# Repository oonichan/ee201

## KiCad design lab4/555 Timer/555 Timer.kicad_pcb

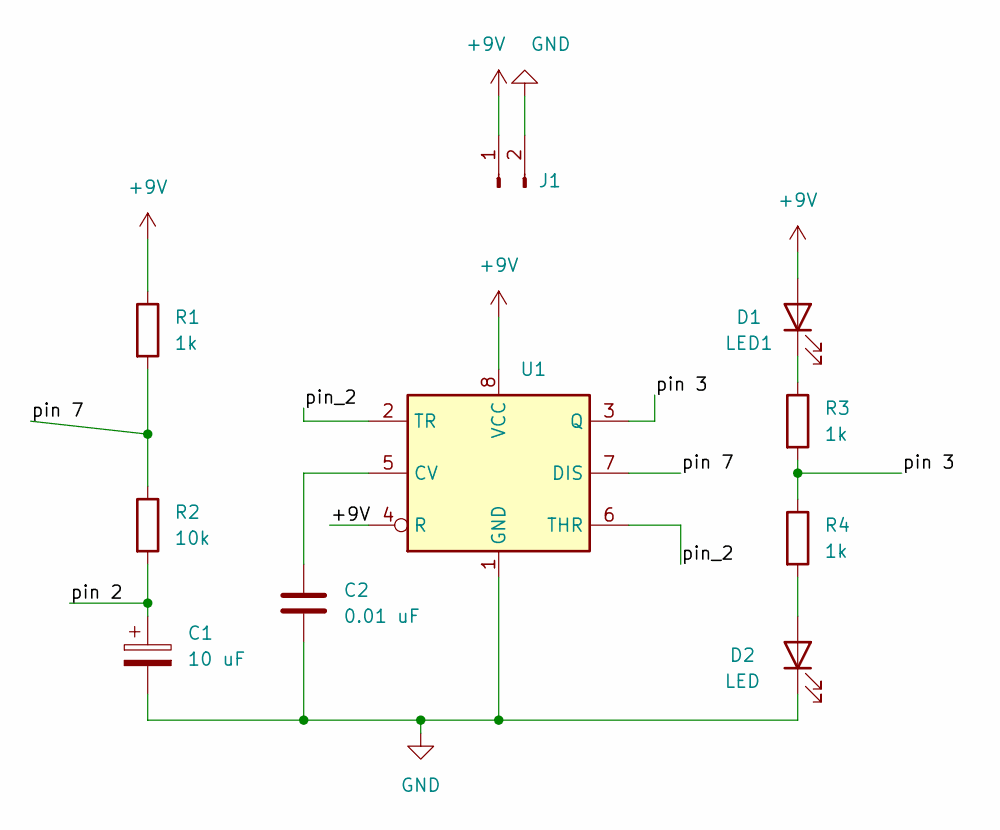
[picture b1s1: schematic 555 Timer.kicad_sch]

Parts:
C1: 10 uF; CP_EIA-3216-18_Kemet-A_Pad1.58x1.35mm_HandSolder
C2: 0.01 uF; C_0805_2012Metric_Pad1.18x1.45mm_HandSolder
D2: LED; LED_1206_3216Metric_Pad1.42x1.75mm_HandSolder
J1: Conn_01x02_Male; TerminalBlock_bornier-2_P5.08mm
LED1: D1; LED_1206_3216Metric_Pad1.42x1.75mm_HandSolder
R1, R3, R4: 1k; R_0805_2012Metric_Pad1.20x1.40mm_HandSolder
R2: 10k; R_0805_2012Metric_Pad1.20x1.40mm_HandSolder
U1: NE555D; SOIC-8-1EP_3.9x4.9mm_P1.27mm_EP2.29x3mm

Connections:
+9V: J1.1, LED1.2 (A), R1.1, U1.4 (R), U1.8 (VCC)
/pin 2: C1.1, R2.2
/pin 3: R3.2, R4.1, U1.3 (Q)
/pin 7: R1.2, R2.1, U1.7 (DIS)
/pin_2: U1.2 (TR), U1.6 (THR)
GND: C1.2, C2.2, D2.1 (K), J1.2, U1.1 (GND)
unnamed: C2.1, U1.5 (CV)
unnamed: D2.2 (A), R4.2
unnamed: LED1.1 (K), R3.1

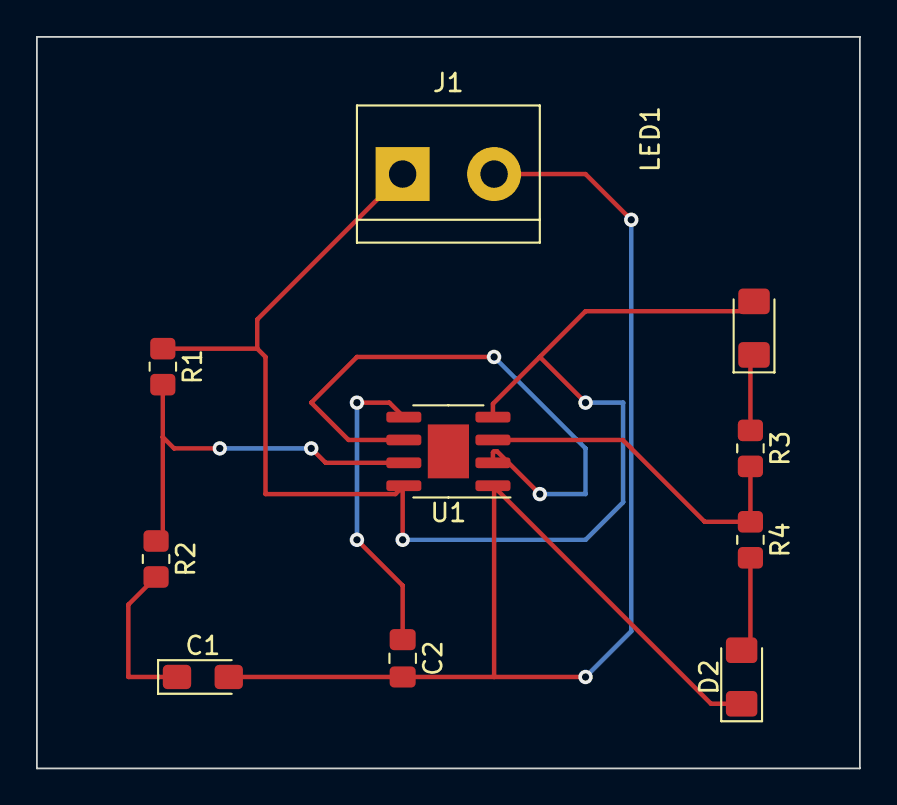
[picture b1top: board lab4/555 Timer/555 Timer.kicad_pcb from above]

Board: 2 copper layers, 45.7 x 40.6 mm, 10 parts (0 on the bottom side), 9 nets.

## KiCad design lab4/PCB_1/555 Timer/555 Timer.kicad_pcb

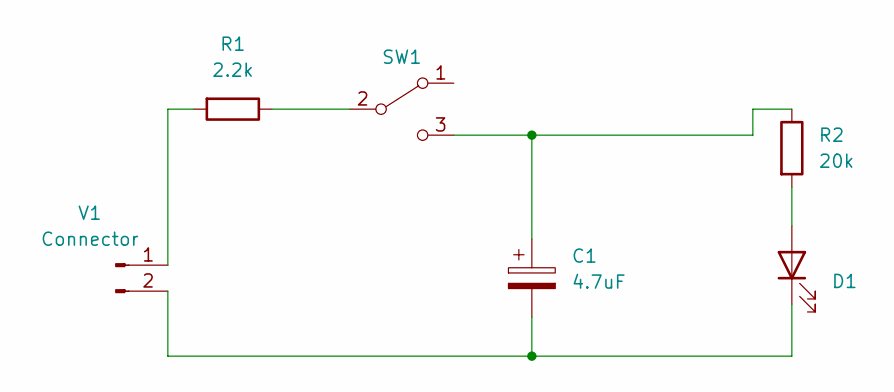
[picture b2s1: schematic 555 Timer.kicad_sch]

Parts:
C1: 4.7uF; C_Radial_D5.0mm_H5.0mm_P2.00mm
D1: LED; LED_D5.0mm
R1: 2.2k; R_Axial_DIN0516_L15.5mm_D5.0mm_P20.32mm_Horizontal
R2: 20k; R_Axial_DIN0516_L15.5mm_D5.0mm_P20.32mm_Horizontal
SW1: SW_SPDT; SW_E-Switch_EG1224_SPDT_Angled
V1: Connector; JST_PH_B2B-PH-K_1x02_P2.00mm_Vertical

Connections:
unnamed: C1.1, R2.1, SW1.3 (C)
unnamed: C1.2, D1.1 (K), V1.2
unnamed: D1.2 (A), R2.2
unnamed: R1.1, SW1.2 (B)
unnamed: R1.2, V1.1

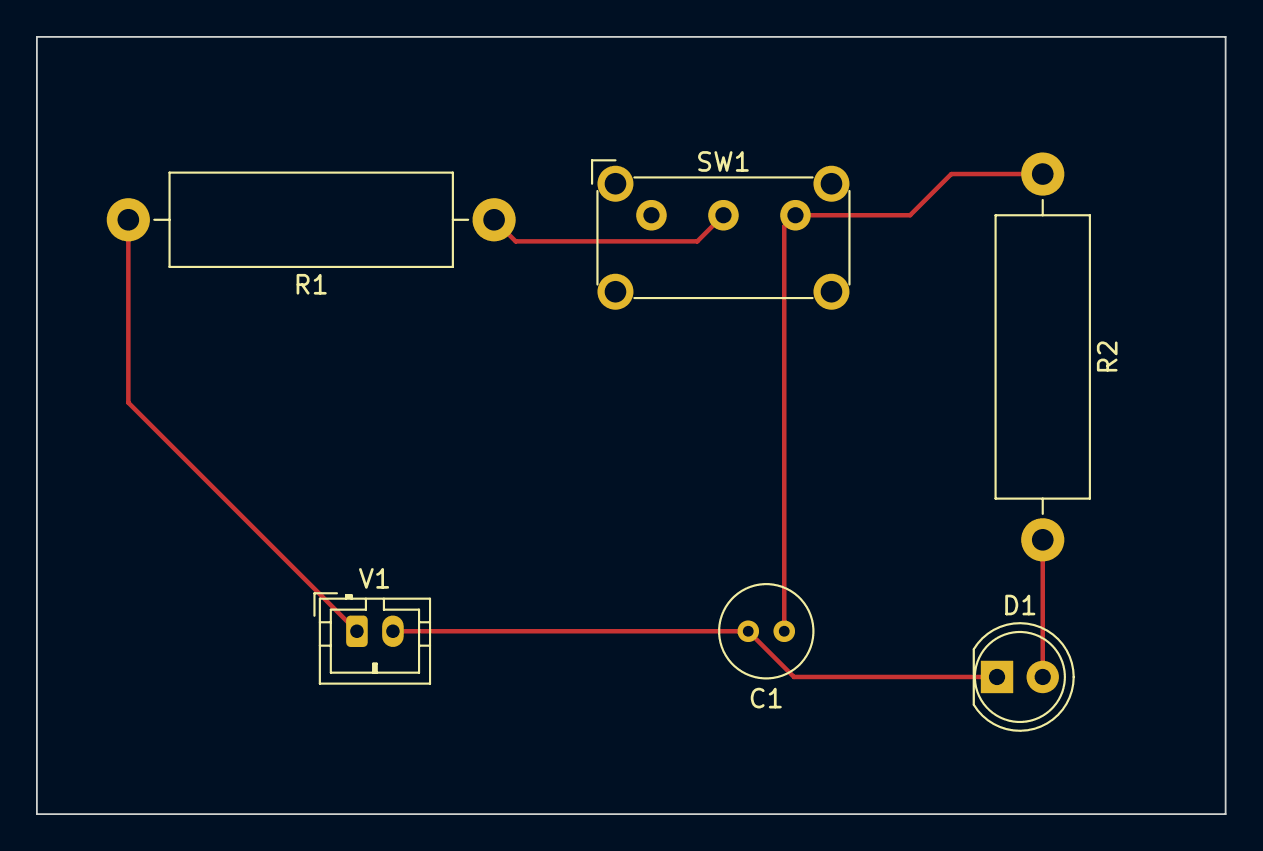
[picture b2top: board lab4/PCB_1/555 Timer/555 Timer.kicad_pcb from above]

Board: 2 copper layers, 66.0 x 43.2 mm, 6 parts (0 on the bottom side), 5 nets.

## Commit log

2023-01-13 Type commit message
2023-01-13 Pushing new branch
2023-01-13 About me!
2023-01-13 my dogs!
2023-01-20 Arduino Lab
2023-01-27 lab4
2023-02-03 soldering
2023-02-10 PCB Design
2023-02-17 solder
2023-02-17 gerber
2023-03-12 arduometer
